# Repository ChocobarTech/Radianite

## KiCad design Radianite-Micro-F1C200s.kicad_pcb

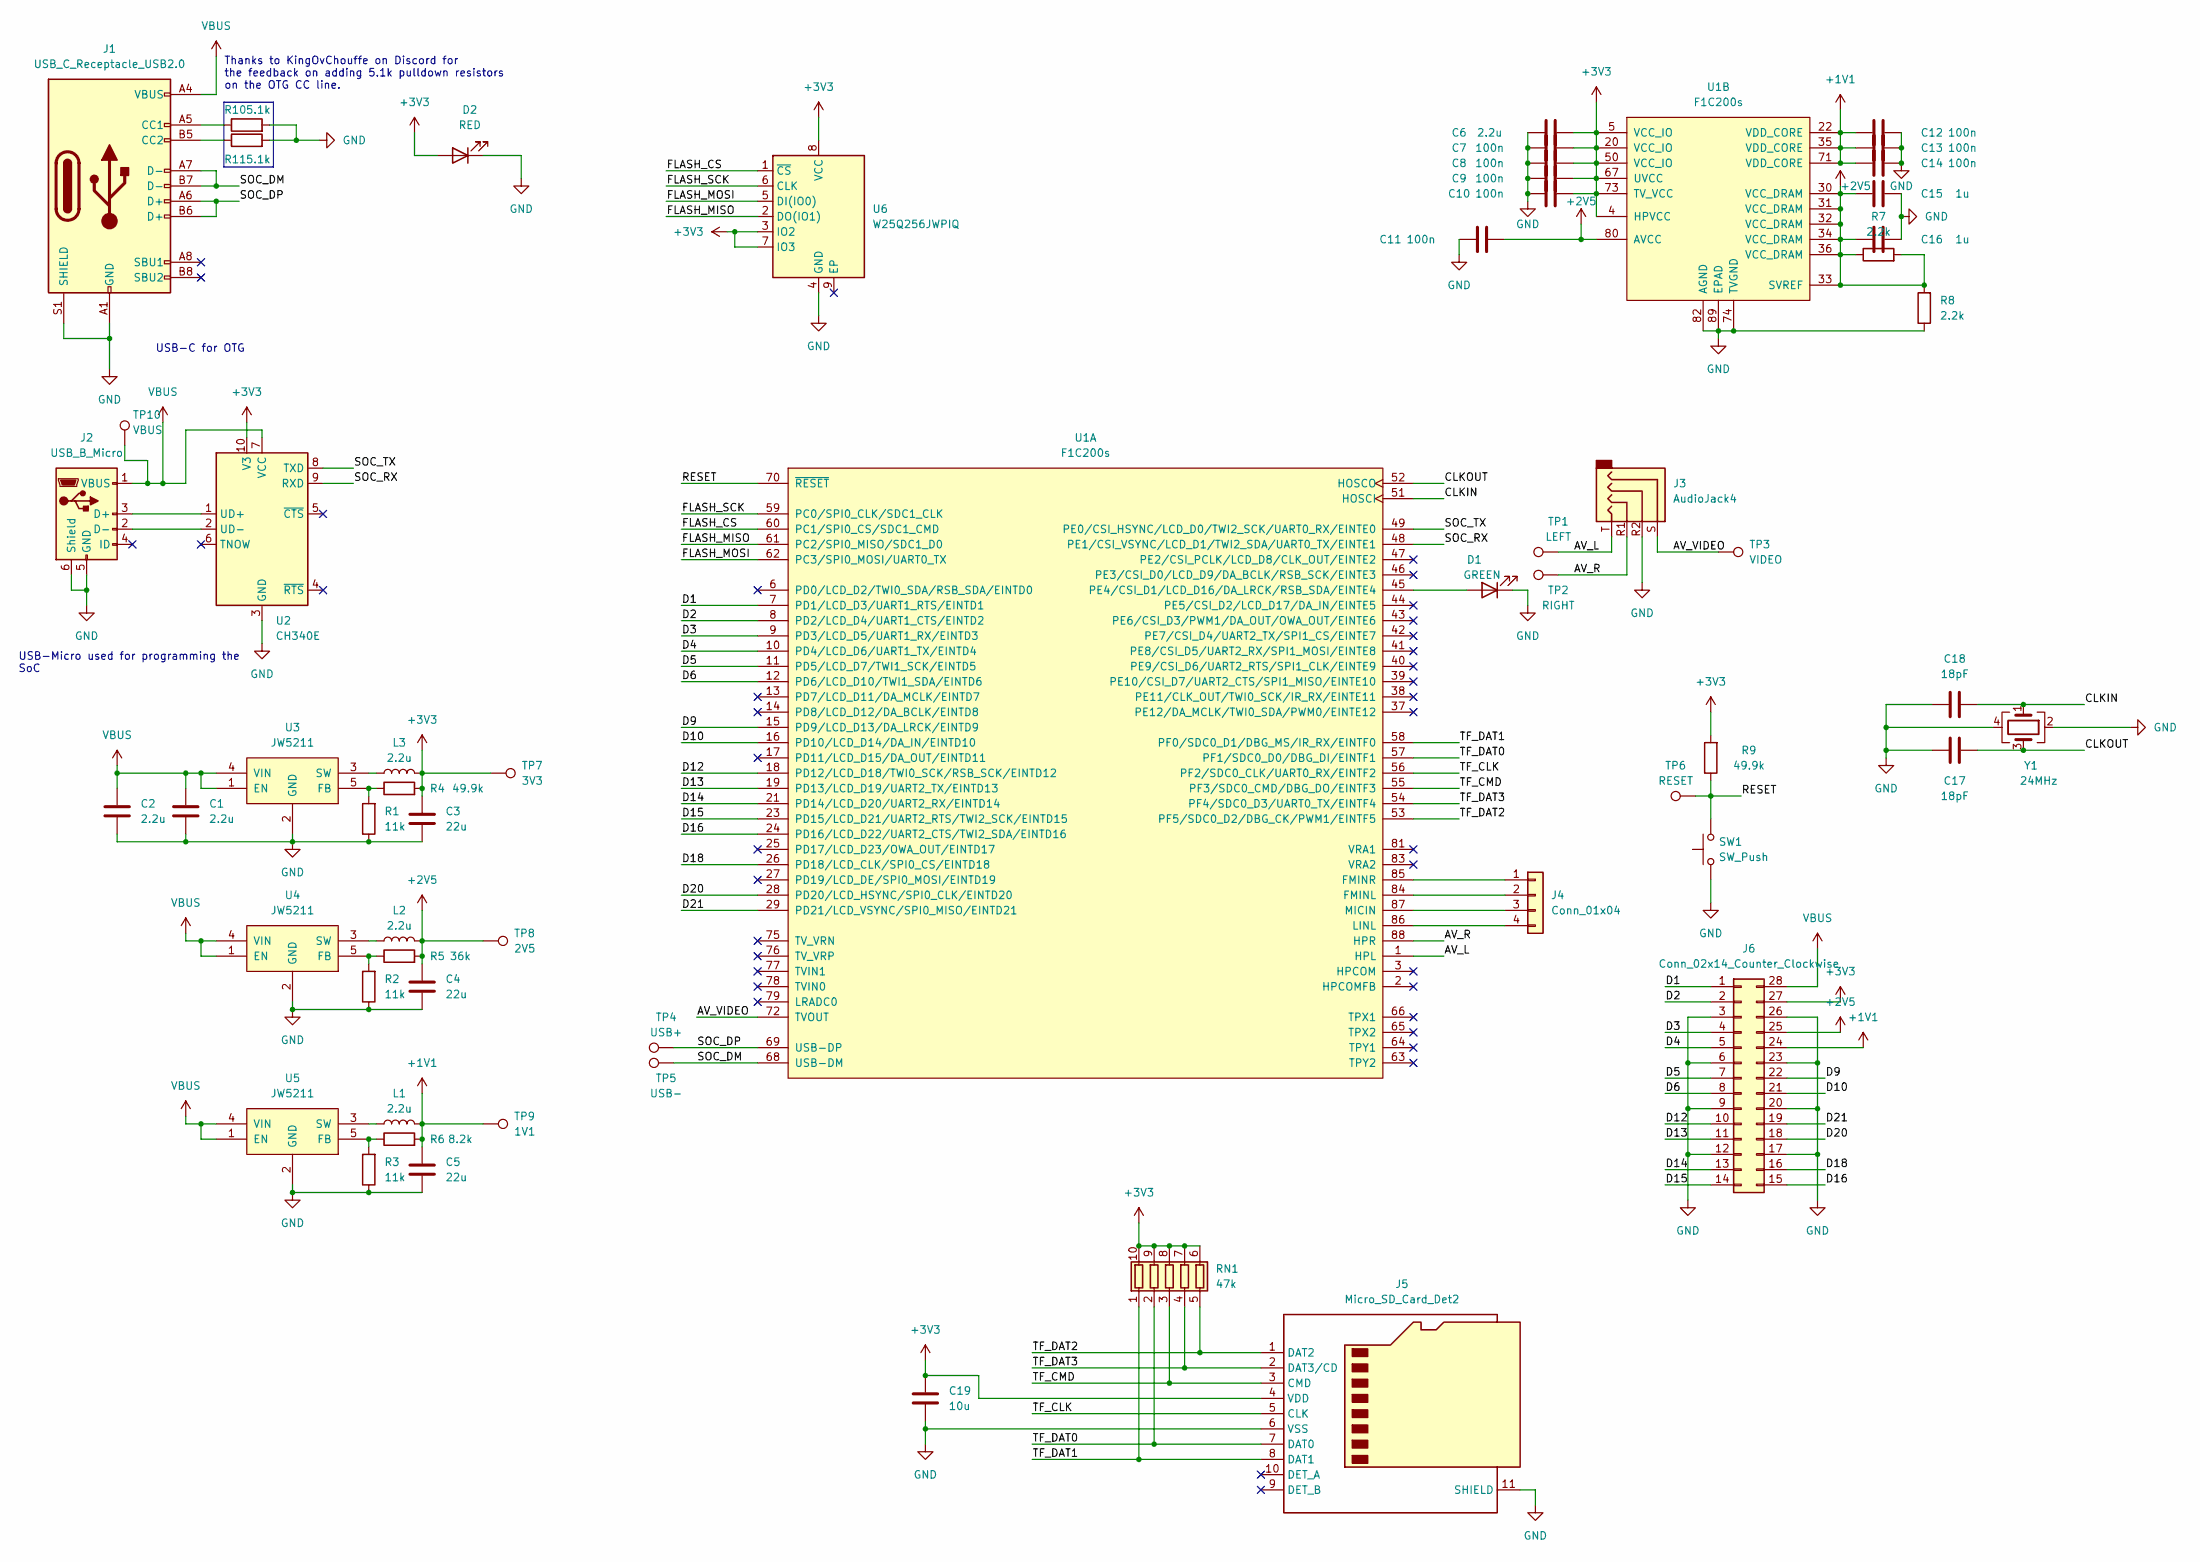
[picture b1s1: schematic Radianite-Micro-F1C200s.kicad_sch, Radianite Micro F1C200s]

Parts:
C1, C2, C6: 2.2u; C_0201_0603Metric
C3, C4, C5: 22u; C_0201_0603Metric
C7, C8, C9, C10, C11, C12, C13, C14: 100n; C_0201_0603Metric
C15, C16: 1u; C_0201_0603Metric
C17, C18: 18pF; C_0201_0603Metric
C19: 10u; C_0201_0603Metric
D1: GREEN; LED_0201_0603Metric
D2: RED; LED_0201_0603Metric
J1: USB_C_Receptacle_USB2.0; USB_C_Receptacle_XKB_U262-16XN-4BVC11
J2: USB_B_Micro; USB_Micro-B_GCT_USB3076-30-A
J3: AudioJack4; Jack_3.5mm_KoreanHropartsElec_PJ-320D-4A_Horizontal
J4: Conn_01x04; PinHeader_1x04_P2.54mm_Vertical
J5: Micro_SD_Card_Det2; microSD_HC_Molex_104031-0811
J6: Conn_02x14_Counter_Clockwise; PinHeader_2x14_P2.54mm_Vertical
L1, L2, L3: 2.2u; L_0402_1005Metric
R1, R2, R3: 11k; R_0201_0603Metric
R4, R9: 49.9k; R_0201_0603Metric
R5: 36k; R_0201_0603Metric
R6: 8.2k; R_0201_0603Metric
R7, R8: 2.2k; R_0201_0603Metric
R10, R11: 5.1k; R_0201_0603Metric
RN1: 47k; R_Array_Convex_5x0603
SW1: SW_Push; SW_Push_1P1T_NO_Vertical_Wuerth_434133025816
TP1: LEFT; TestPoint_Pad_D1.0mm
TP2: RIGHT; TestPoint_Pad_D1.0mm
TP3: VIDEO; TestPoint_Pad_D1.0mm
TP4: USB+; TestPoint_Pad_D1.0mm
TP5: USB-; TestPoint_Pad_D1.0mm
TP6: RESET; TestPoint_Pad_D1.0mm
TP7: 3V3; TestPoint_Pad_D1.0mm
TP8: 2V5; TestPoint_Pad_D1.0mm
TP9: 1V1; TestPoint_Pad_D1.0mm
TP10: VBUS; TestPoint_Pad_D1.0mm
U1: F1C200s; QFN-88_EP_10x10_Pitch0.4mm
U2: CH340E; MSOP-10_3x3mm_P0.5mm
U3, U4, U5: JW5211; SOT-23-5
U6: W25Q256JWPIQ; WSON-8-1EP_6x5mm_P1.27mm_EP3.4x4.3mm
Y1: 24MHz; Crystal_SMD_2520-4Pin_2.5x2.0mm

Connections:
+1V1: C5.1, C12.1, C13.1, C14.1, J6.24, L1.2, R6.2, TP9.1, U1.22 (VDD_CORE), U1.35 (VDD_CORE), U1.71 (VDD_CORE)
+2V5: C4.1, C11.2, C15.1, C16.1, J6.25, L2.2, R5.2, R7.1, R7.2, R8.2, TP8.1, U1.30 (VCC_DRAM), U1.31 (VCC_DRAM), U1.32 (VCC_DRAM), U1.33 (SVREF), U1.34 (VCC_DRAM), U1.36 (VCC_DRAM), U1.80 (AVCC)
+3V3: C3.1, C6.2, C7.2, C8.2, C9.2, C10.2, C19.1, D2.2 (A), J5.4 (VDD), J6.27, L3.2, R4.2, R9.2, RN1.6 (R5.2), RN1.7 (R4.2), RN1.8 (R3.2), RN1.9 (R2.2), RN1.10 (R1.2), TP7.1, U1.4 (HPVCC), U1.5 (VCC_IO), U1.20 (VCC_IO), U1.50 (VCC_IO), U1.67 (UVCC), U1.73 (TV_VCC), U2.10 (V3), U6.3 (IO2), U6.7 (IO3), U6.8 (VCC)
/AV_L: J3.T, TP1.1, U1.1 (HPL)
/AV_R: J3.R1, TP2.1, U1.88 (HPR)
/AV_VIDEO: J3.S, TP3.1, U1.72 (TVOUT)
/CLKIN: C18.2, U1.51 (HOSCI), Y1.1
/CLKOUT: C17.1, U1.52 (HOSCO), Y1.3
/D1: J6.1, U1.7 (PD1/LCD_D3/UART1_RTS/EINTD1)
/D2: J6.2, U1.8 (PD2/LCD_D4/UART1_CTS/EINTD2)
/D3: J6.4, U1.9 (PD3/LCD_D5/UART1_RX/EINTD3)
/D4: J6.5, U1.10 (PD4/LCD_D6/UART1_TX/EINTD4)
/D5: J6.7, U1.11 (PD5/LCD_D7/TWI1_SCK/EINTD5)
/D6: J6.8, U1.12 (PD6/LCD_D10/TWI1_SDA/EINTD6)
/D9: J6.22, U1.15 (PD9/LCD_D13/DA_LRCK/EINTD9)
/D10: J6.21, U1.16 (PD10/LCD_D14/DA_IN/EINTD10)
/D12: J6.10, U1.18 (PD12/LCD_D18/TWI0_SCK/RSB_SCK/EINTD12)
/D13: J6.11, U1.19 (PD13/LCD_D19/UART2_TX/EINTD13)
/D14: J6.13, U1.21 (PD14/LCD_D20/UART2_RX/EINTD14)
/D15: J6.14, U1.23 (PD15/LCD_D21/UART2_RTS/TWI2_SCK/EINTD15)
/D16: J6.15, U1.24 (PD16/LCD_D22/UART2_CTS/TWI2_SDA/EINTD16)
/D18: J6.16, U1.26 (PD18/LCD_CLK/SPI0_CS/EINTD18)
/D20: J6.18, U1.28 (PD20/LCD_HSYNC/SPI0_CLK/EINTD20)
/D21: J6.19, U1.29 (PD21/LCD_VSYNC/SPI0_MISO/EINTD21)
/FLASH_CS: U1.60 (PC1/SPI0_CS/SDC1_CMD), U6.1 (~CS)
/FLASH_MISO: U1.61 (PC2/SPI0_MISO/SDC1_D0), U6.2 (DO(IO1))
/FLASH_MOSI: U1.62 (PC3/SPI0_MOSI/UART0_TX), U6.5 (DI(IO0))
/FLASH_SCK: U1.59 (PC0/SPI0_CLK/SDC1_CLK), U6.6 (CLK)
/RESET: R9.1, SW1.2, TP6.1, U1.70 (~RESET)
/SOC_DM: J1.A7 (D-), J1.B7 (D-), TP5.1, U1.68 (USB-DM)
/SOC_DP: J1.A6 (D+), J1.B6 (D+), TP4.1, U1.69 (USB-DP)
/SOC_RX: U1.48 (PE1/CSI_VSYNC/LCD_D1/TWI2_SDA/UART0_TX/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), U2.9 (RXD)
/SOC_TX: U1.49 (PE0/CSI_HSYNC/LCD_D0/TWI2_SCK/UART0_RX/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), U2.8 (TXD)
/TF_CLK: J5.5 (CLK), U1.56 (PF2/SDC0_CLK/UART0_RX/EINTF2)
/TF_CMD: J5.3 (CMD), RN1.3 (R3.1), U1.55 (PF3/SDC0_CMD/DBG_DO/EINTF3)
/TF_DAT0: J5.7 (DAT0), RN1.2 (R2.1), U1.57 (PF1/SDC0_D0/DBG_DI/EINTF1)
/TF_DAT1: J5.8 (DAT1), RN1.1 (R1.1), U1.58 (PF0/SDC0_D1/DBG_MS/IR_RX/EINTF0)
/TF_DAT2: J5.1 (DAT2), RN1.5 (R5.1), U1.53 (PF5/SDC0_D2/DBG_CK/PWM1/EINTF5)
/TF_DAT3: J5.2 (DAT3/CD), RN1.4 (R4.1), U1.54 (PF4/SDC0_D3/UART0_TX/EINTF4)
GND: C1.2, C2.2, C3.2, C4.2, C5.2, C6.1, C7.1, C8.1, C9.1, C10.1, C11.1, C12.2, C13.2, C14.2, C15.2, C16.2, C17.2, C18.1, C19.2, D1.1 (K), D2.1 (K), J1.A1 (GND), J1.A12 (GND), J1.B1 (GND), J1.B12 (GND), J1.S1 (SHIELD), J2.5 (GND), J2.6 (Shield), J3.R2, J5.6 (VSS), J5.11 (SHIELD), J6.3, J6.6, J6.9, J6.12, J6.17, J6.20, J6.23, J6.26, R1.1, R2.1, R3.1, R8.1, R10.2, R11.2, SW1.1, U1.74 (TVGND), U1.82 (AGND), U1.89 (EPAD), U2.3 (GND), U3.2 (GND), U4.2 (GND), U5.2 (GND), U6.4 (GND), Y1.2, Y1.4
unnamed: D1.2 (A), U1.45 (PE4/CSI_D1/LCD_D16/DA_LRCK/RSB_SDA/EINT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)
unnamed: J1.A5 (CC1), R10.1
unnamed: J1.B5 (CC2), R11.1
unnamed: J2.3 (D+), U2.1 (UD+)
unnamed: J2.2 (D-), U2.2 (UD-)
unnamed: J4.1, U1.85 (FMINR)
unnamed: J4.2, U1.84 (FMINL)
unnamed: J4.3, U1.87 (MICIN)
unnamed: J4.4, U1.86 (LINL)
unnamed: R1.2, R4.1, U3.5 (FB)
unnamed: L3.1, U3.3 (SW)
unnamed: R2.2, R5.1, U4.5 (FB)
unnamed: L2.1, U4.3 (SW)
unnamed: R3.2, R6.1, U5.5 (FB)
unnamed: L1.1, U5.3 (SW)
VBUS: C1.1, C2.1, J1.A4 (VBUS), J1.A9 (VBUS), J1.B4 (VBUS), J1.B9 (VBUS), J2.1 (VBUS), J6.28, TP10.1, U2.7 (VCC), U3.1 (EN), U3.4 (VIN), U4.1 (EN), U4.4 (VIN), U5.1 (EN), U5.4 (VIN)

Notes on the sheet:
USB-Micro used for programming the SoC
USB-C for OTG
Thanks to KingOvChouffe on Discord for the feedback on adding 5.1k pulldown resistors on the OTG CC line.

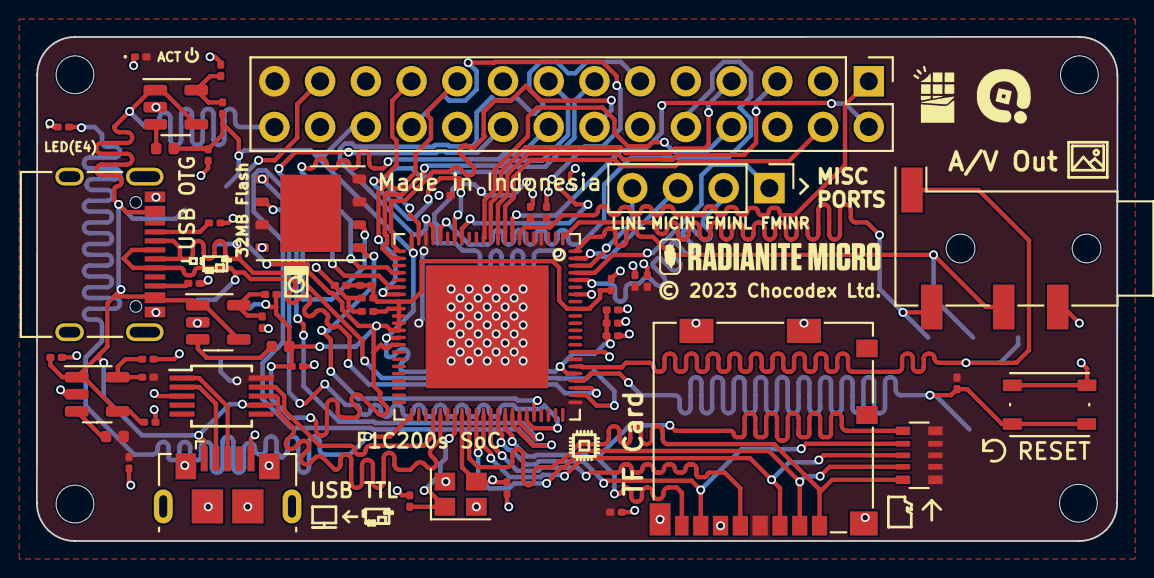
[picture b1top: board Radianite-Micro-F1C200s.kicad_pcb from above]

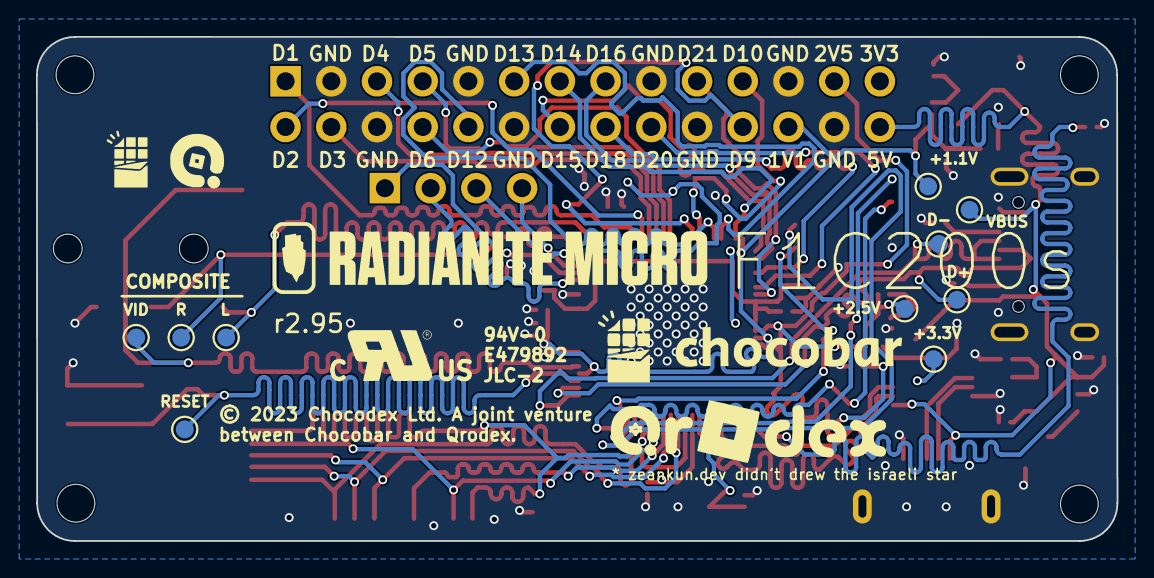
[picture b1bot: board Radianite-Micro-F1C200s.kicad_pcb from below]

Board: 2 copper layers, 60.0 x 28.0 mm, 60 parts (10 on the bottom side), 56 nets.

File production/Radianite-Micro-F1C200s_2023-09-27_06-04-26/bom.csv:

Designator,Footprint,Quantity,Value,LCSC Part #
"C1, C2, C6",0201,3,2.2u,
"C10, C11, C12, C13, C14, C7, C8, C9",0201,8,100n,
"C15, C16",0201,2,1u,
"C17, C18",0201,2,18pF,
C19,0201,1,10u,
"C3, C4, C5",0201,3,22u,
D1,0201,1,GREEN,
D2,0201,1,RED,
J1,USB_C_Receptacle_XKB_U262-16XN-4BVC11,1,USB_C_Receptacle_USB2.0,
J2,USB_Micro-B_GCT_USB3076-30-A,1,USB_B_Micro,
J3,Jack_3.5mm_KoreanHropartsElec_PJ-320D-4A_Horizontal,1,AudioJack4,
J4,PinHeader_1x04_P2.54mm_Vertical,1,Conn_01x04,
J5,microSD_HC_Molex_104031-0811,1,Micro_SD_Card_Det2,
J6,PinHeader_2x14_P2.54mm_Vertical,1,Conn_02x14_Counter_Clockwise,
"L1, L2, L3",0402,3,2.2u,
"R1, R2, R3",0201,3,11k,
"R4, R9",0201,2,49.9k,
R5,0201,1,36k,
R6,0201,1,8.2k,
"R7, R8",0201,2,2.2k,
RN1,R_Array_Convex_5x0603,1,47k,
SW1,SW_Push_1P1T_NO_Vertical_Wuerth_434133025816,1,SW_Push,
U1,QFN-88_EP_10x10_Pitch0.4mm,1,F1C200s,
U2,MSOP-10_3x3mm_P0.5mm,1,CH340E,
"U3, U4, U5",SOT-23-5,3,JW5211,
U6,WSON-8-1EP_6x5mm_P1.27mm_EP3.4x4.3mm,1,W25Q256JWPIQ,
Y1,Crystal_SMD_2520-4Pin_2.5x2.0mm,1,24MHz,

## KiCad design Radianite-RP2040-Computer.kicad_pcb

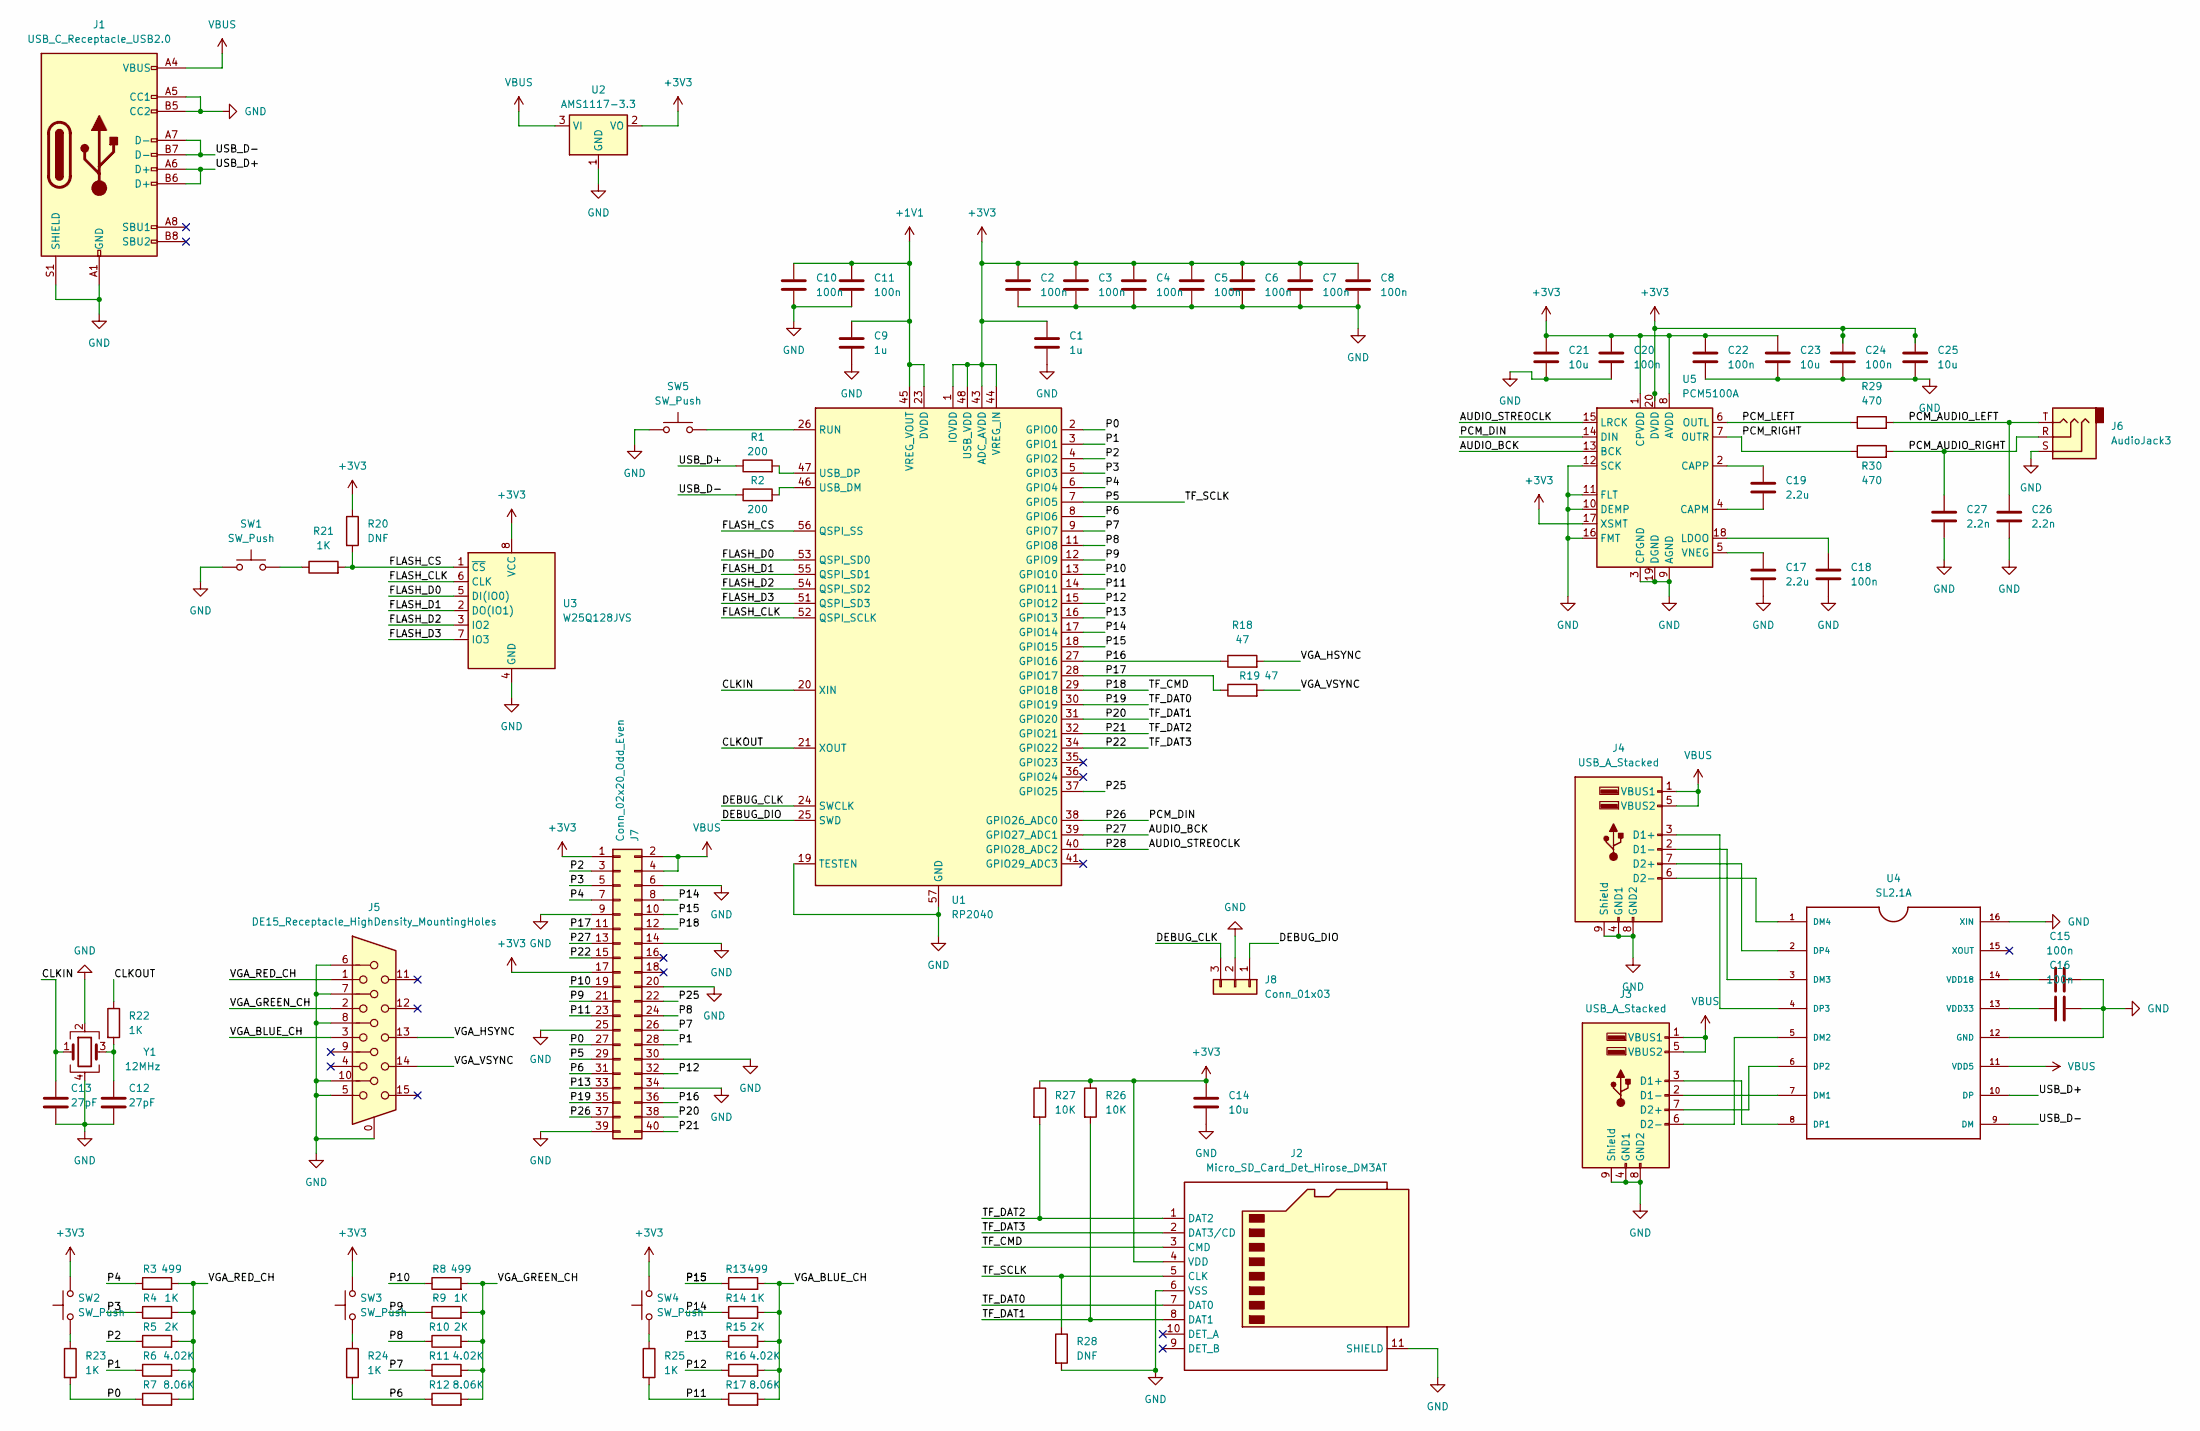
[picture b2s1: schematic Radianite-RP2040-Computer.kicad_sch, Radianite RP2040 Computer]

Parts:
C1, C9: 1u; C_0201_0603Metric
C2, C3, C4, C5, C6, C7, C8, C10, C11, C15, C16, C18, C20, C22, C24: 100n; C_0201_0603Metric
C12, C13: 27pF; C_0201_0603Metric
C14, C21, C23, C25: 10u; C_0201_0603Metric
C17, C19: 2.2u; C_0201_0603Metric
C26, C27: 2.2n; C_0201_0603Metric
J1: USB_C_Receptacle_USB2.0; USB_C_Receptacle_GCT_USB4105-xx-A_16P_TopMnt_Horizontal
J2: Micro_SD_Card_Det_Hirose_DM3AT; microSD_HC_Molex_104031-0811
J3, J4: USB_A_Stacked; USB_A_CUI_UJ2-ADH-TH_Horizontal_Stacked
J5: DE15_Receptacle_HighDensity_MountingHoles; DSUB-15-HD_Female_Horizontal_P2.29x1.98mm_EdgePinOffset3.03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
J6: AudioJack3; Jack_3.5mm_CUI_SJ-3523-SMT_Horizontal
J7: Conn_02x20_Odd_Even; PinHeader_2x20_P2.54mm_Vertical
J8: Conn_01x03; PinHeader_1x03_P2.54mm_Vertical
R1, R2: 200; R_0201_0603Metric
R3, R8, R13: 499; R_0201_0603Metric
R4, R9, R14, R21, R22, R23, R24, R25: 1K; R_0201_0603Metric
R5, R10, R15: 2K; R_0201_0603Metric
R6, R11, R16: 4.02K; R_0201_0603Metric
R7, R12, R17: 8.06K; R_0201_0603Metric
R18, R19: 47; R_0201_0603Metric
R20, R28: DNF; R_0201_0603Metric
R26, R27: 10K; R_0201_0603Metric
R29, R30: 470; R_0201_0603Metric
SW1, SW2, SW3, SW4, SW5: SW_Push; SW_Push_1P1T_NO_Vertical_Wuerth_434133025816
U1: RP2040; QFN-56-1EP_7x7mm_P0.4mm_EP3.2x3.2mm
U2: AMS1117-3.3; SOT-223-3_TabPin2
U3: W25Q128JVS; SOIC-8_5.23x5.23mm_P1.27mm
U4: SL2.1A; SO16
U5: PCM5100A; TSSOP-20_4.4x6.5mm_P0.65mm
Y1: 12MHz; Crystal_SMD_7050-4Pin_7.0x5.0mm

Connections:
+1V1: C9.1, C10.1, C11.1, U1.23 (DVDD), U1.45 (VREG_VOUT), U1.50 (DVDD)
+3V3: C1.1, C2.1, C3.1, C4.1, C5.1, C6.1, C7.1, C8.1, C14.1, C20.1, C21.1, C22.1, C23.1, C24.1, C25.1, J2.4 (VDD), J7.1, J7.17, R20.1, R26.1, R27.1, SW2.2, SW3.2, SW4.2, U1.1 (IOVDD), U1.10 (IOVDD), U1.22 (IOVDD), U1.33 (IOVDD), U1.42 (IOVDD), U1.43 (ADC_AVDD), U1.44 (VREG_IN), U1.48 (USB_VDD), U1.49 (IOVDD), U2.2 (VO), U3.8 (VCC), U5.1 (CPVDD), U5.8 (AVDD), U5.17 (XSMT), U5.20 (DVDD)
/AUDIO_BCK: J7.13, U1.39 (GPIO27_ADC1), U5.13 (BCK)
/AUDIO_STREOCLK: U1.40 (GPIO28_ADC2), U5.15 (LRCK)
/CLKIN: C13.1, U1.20 (XIN), Y1.1
/CLKOUT: R22.1, U1.21 (XOUT)
/DEBUG_CLK: J8.3, U1.24 (SWCLK)
/DEBUG_DIO: J8.1, U1.25 (SWD)
/FLASH_CLK: U1.52 (QSPI_SCLK), U3.6 (CLK)
/FLASH_CS: R20.2, R21.2, U1.56 (QSPI_SS), U3.1 (~CS)
/FLASH_D0: U1.53 (QSPI_SD0), U3.5 (DI(IO0))
/FLASH_D1: U1.55 (QSPI_SD1), U3.2 (DO(IO1))
/FLASH_D2: U1.54 (QSPI_SD2), U3.3 (IO2)
/FLASH_D3: U1.51 (QSPI_SD3), U3.7 (IO3)
/P0: J7.27, R7.1, R23.2, U1.2 (GPIO0)
/P1: J7.28, R6.1, U1.3 (GPIO1)
/P2: J7.3, R5.1, U1.4 (GPIO2)
/P3: J7.5, R4.1, U1.5 (GPIO3)
/P4: J7.7, R3.1, U1.6 (GPIO4)
/P5: J2.5 (CLK), J7.29, R28.1, U1.7 (GPIO5)
/P6: J7.31, R12.1, R24.2, U1.8 (GPIO6)
/P7: J7.26, R11.1, U1.9 (GPIO7)
/P8: J7.24, R10.1, U1.11 (GPIO8)
/P9: J7.21, R9.1, U1.12 (GPIO9)
/P10: J7.19, R8.1, U1.13 (GPIO10)
/P11: J7.23, R17.1, R25.2, U1.14 (GPIO11)
/P12: J7.32, R16.1, U1.15 (GPIO12)
/P13: J7.33, R15.1, U1.16 (GPIO13)
/P14: J7.8, R14.1, U1.17 (GPIO14)
/P15: J7.10, R13.1, U1.18 (GPIO15)
/P16: J7.36, R18.1, U1.27 (GPIO16)
/P17: J7.11, R19.1, U1.28 (GPIO17)
/P18: J2.3 (CMD), J7.12, U1.29 (GPIO18)
/P19: J2.7 (DAT0), J7.35, U1.30 (GPIO19)
/P20: J2.8 (DAT1), J7.38, R26.2, U1.31 (GPIO20)
/P21: J2.1 (DAT2), J7.40, R27.2, U1.32 (GPIO21)
/P22: J2.2 (DAT3/CD), J7.15, U1.34 (GPIO22)
/P25: J7.22, U1.37 (GPIO25)
/P26: J7.37, U1.38 (GPIO26_ADC0), U5.14 (DIN)
/PCM_AUDIO_LEFT: C26.1, J6.T, R29.2
/PCM_AUDIO_RIGHT: C27.1, J6.R, R30.2
/PCM_LEFT: R29.1, U5.6 (OUTL)
/PCM_RIGHT: R30.1, U5.7 (OUTR)
/USB_D+: J1.A6 (D+), J1.B6 (D+), R1.1, U4.10 (DP)
/USB_D-: J1.A7 (D-), J1.B7 (D-), R2.1, U4.9 (DM)
/VGA_BLUE_CH: J5.3, R13.2, R14.2, R15.2, R16.2, R17.2
/VGA_GREEN_CH: J5.2, R8.2, R9.2, R10.2, R11.2, R12.2
/VGA_HSYNC: J5.13, R18.2
/VGA_RED_CH: J5.1, R3.2, R4.2, R5.2, R6.2, R7.2
/VGA_VSYNC: J5.14, R19.2
GND: C1.2, C2.2, C3.2, C4.2, C5.2, C6.2, C7.2, C8.2, C9.2, C10.2, C11.2, C12.2, C13.2, C14.2, C15.2, C16.2, C17.2, C18.2, C20.2, C21.2, C22.2, C23.2, C24.2, C25.2, C26.2, C27.2, J1.A1 (GND), J1.A5 (CC1), J1.A12 (GND), J1.B1 (GND), J1.B5 (CC2), J1.B12 (GND), J1.S1 (SHIELD), J2.6 (VSS), J2.11 (SHIELD), J3.4 (GND1), J3.8 (GND2), J3.9 (Shield), J4.4 (GND1), J4.8 (GND2), J4.9 (Shield), J5.0, J5.5, J5.6, J5.7, J5.8, J5.10, J6.S, J7.6, J7.9, J7.14, J7.20, J7.25, J7.30, J7.34, J7.39, J8.2, R28.2, SW1.1, SW5.1, U1.19 (TESTEN), U1.57 (GND), U2.1 (GND), U3.4 (GND), U4.12 (GND), U4.16 (XIN), U5.3 (CPGND), U5.9 (AGND), U5.10 (DEMP), U5.11 (FLT), U5.12 (SCK), U5.16 (FMT), U5.19 (DGND), Y1.2, Y1.4
unnamed: C12.1, R22.2, Y1.3
unnamed: J3.3 (D1+), U4.8 (DP1)
unnamed: J3.2 (D1-), U4.7 (DM1)
unnamed: J3.7 (D2+), U4.6 (DP2)
unnamed: J3.6 (D2-), U4.5 (DM2)
unnamed: J4.3 (D1+), U4.4 (DP3)
unnamed: J4.2 (D1-), U4.3 (DM3)
unnamed: J4.7 (D2+), U4.2 (DP4)
unnamed: J4.6 (D2-), U4.1 (DM4)
unnamed: R21.1, SW1.2
unnamed: R23.1, SW2.1
unnamed: R24.1, SW3.1
unnamed: R25.1, SW4.1
unnamed: SW5.2, U1.26 (RUN)
unnamed: R2.2, U1.46 (USB_DM)
unnamed: R1.2, U1.47 (USB_DP)
unnamed: C15.1, U4.14 (VDD18)
unnamed: C16.1, U4.13 (VDD33)
unnamed: C19.2, U5.4 (CAPM)
unnamed: C19.1, U5.2 (CAPP)
unnamed: C18.1, U5.18 (LDOO)
unnamed: C17.1, U5.5 (VNEG)
VBUS: J1.A4 (VBUS), J1.A9 (VBUS), J1.B4 (VBUS), J1.B9 (VBUS), J3.1 (VBUS1), J3.5 (VBUS2), J4.1 (VBUS1), J4.5 (VBUS2), J7.2, J7.4, U2.3 (VI), U4.11 (VDD5)

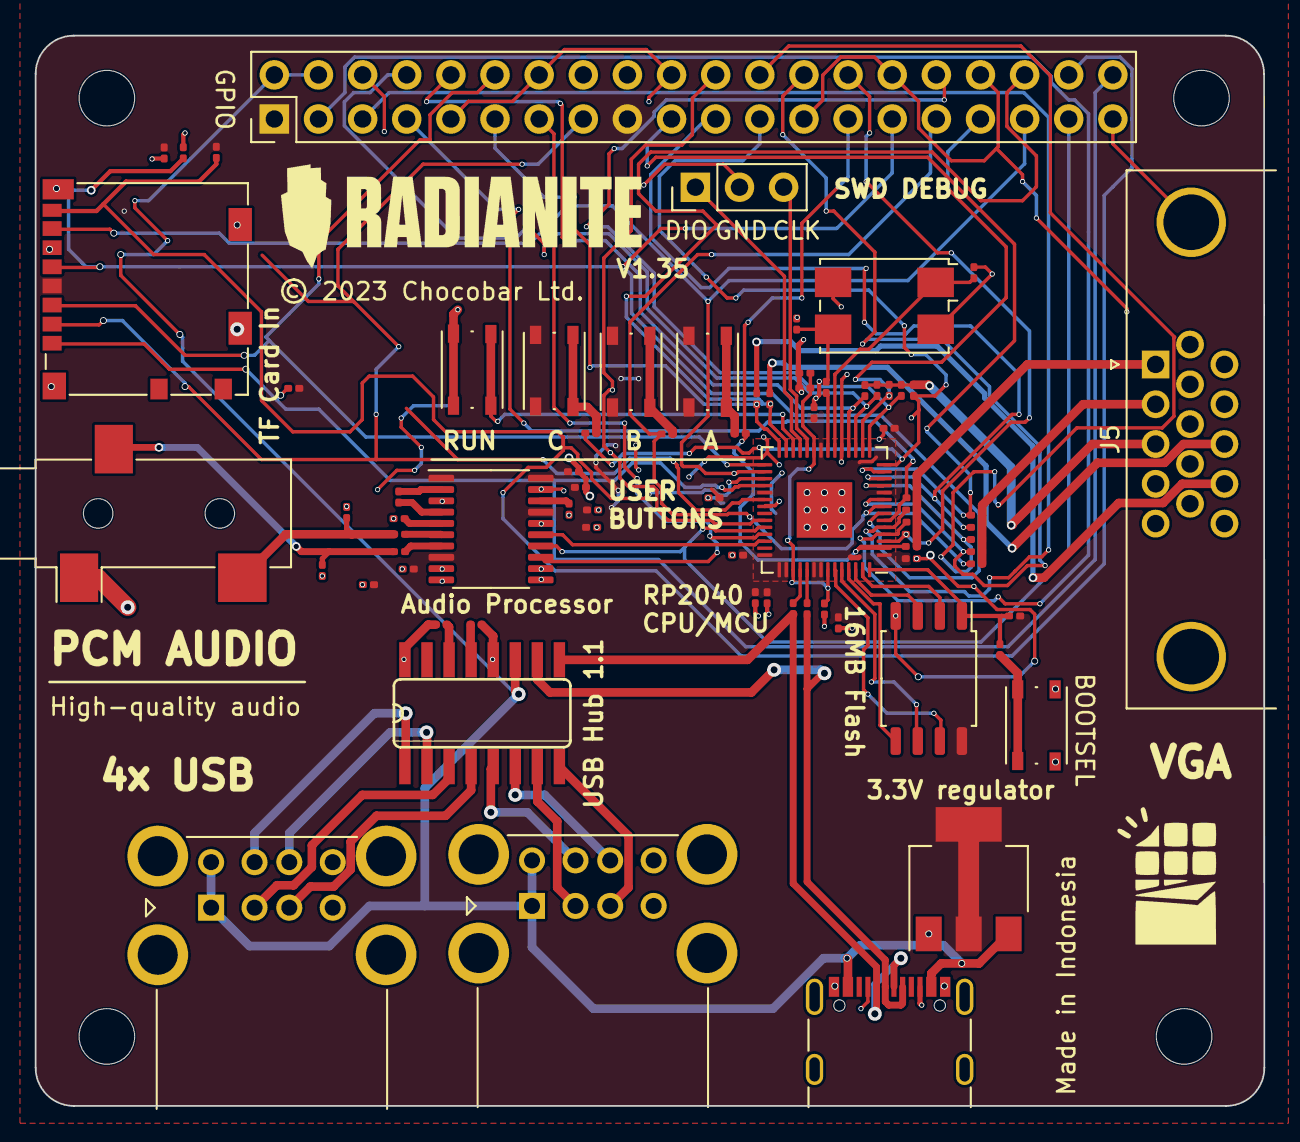
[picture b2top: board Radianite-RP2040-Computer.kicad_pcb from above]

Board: 2 copper layers, 70.7 x 61.6 mm, 76 parts (0 on the bottom side), 74 nets.

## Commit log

2023-11-01 Fix viewport bug on most of the website
2023-11-02 Fix getting-started URL bug
2023-11-19 2.9 change on micro
2023-11-19 revise to length tune track
2023-11-19 fix gnd plane issue
2023-11-20 minor drawing revision
2023-11-29 Some minor stuff + panelization + KiKit config file
2023-11-29 Via violation fixed on net J4-Pin_3
2023-12-02 declare v2.95

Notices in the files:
Radianite-Micro-F1C200s.kicad_pcb:
© 2023 Chocodex Ltd. A joint venture
Radianite-RP2040-Computer.kicad_pcb:
© 2023 Chocobar Ltd.
Radianite-RP2040-Computer.kicad_sch:
(c) 2023 zeankun.dev
